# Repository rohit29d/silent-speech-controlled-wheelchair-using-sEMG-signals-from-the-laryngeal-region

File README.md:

# Hands-Free sEMG-Based Silent Speech Controlled Wheelchair System

[-blue?style=flat-square)](firmware/)

[-blue?style=flat-square)](ml_pipeline/)

> **Academic Notice**: This repository documents undergraduate capstone thesis research conducted at Amrita School of Engineering (March 2026). A formal manuscript publication currently in progress. All materials are shared for admissions review and non-commercial academic evaluation. For collaborative research access or hardware replication inquiries, please contact the author.

A complete end-to-end biomedical cyber-physical assistive system translating non-auditory surface electromyography (sEMG) bio-potentials from laryngeal musculature into real-time directional commands for an electric wheelchair. 

The architecture encompasses a custom multi-stage discrete Analog Front-End (AFE) PCB, an 8 kHz signal acquisition and digital feature extraction pipeline, a Bayesian-optimized Random Forest classifier, and a real-time embedded motor controller with ultrasonic safety interrupts implemented on an ARM Cortex-M7 microcontroller.

---

## System Overview & Clinical Motivation

Conventional assistive interfaces such as mechanical joysticks, sip-and-puff switches, or acoustic voice recognition present severe operational constraints for individuals with profound motor and speech impairments (e.g., Amyotrophic Lateral Sclerosis, locked-in syndrome, quadriplegia). While prior systems investigate ocular tracking, head gestures, or limb electromyography, individuals with advanced quadriplegia combined with vocal cord impairment retain intact cranial nerve pathways governing laryngeal and submental musculature.

During silent articulation (mouthing navigation words without acoustic vocalization), intrinsic and extrinsic laryngeal muscles produce repeatable neuromuscular bio-potentials. Capturing these microvolt signals via a dedicated, low-noise analog front-end provides an acoustic-noise-immune human-machine interface for powered wheelchair navigation.

> **Feasibility & Engineering Scope**: This system serves as a proof-of-concept feasibility platform demonstrating that laryngeal sEMG signals can reliably actuate an electric wheelchair in real time. While clinical adoption warrants non-invasive conformal electrode housings, this work proves that closed-loop silent articulation classification is achievable on embedded microcontroller hardware.

```
+-------------------------------------------------------------------------------------------------------------------------+
|                                                END-TO-END SYSTEM PIPELINE                                               |
+-------------------------------------------------------------------------------------------------------------------------+
```

---

## 1. Hardware & Analog Front-End (AFE)

Laryngeal sEMG signals exhibit low amplitudes ($\approx 10\ \mu\text{V} - 500\ \mu\text{V}$) and are highly vulnerable to motion artifacts, electrode polarization drift, and 50 Hz electromagnetic power-line interference. A dedicated 3-stage analog front-end was designed, simulated in LTspice, and fabricated as a compact 2-layer PCB.

### Circuit Topology & Component Selection

1. **Electrode Configuration**:
   - Differential 3-electrode montage using clinical-grade Ag/AgCl wet gel patches: two electrodes placed over the submental and ventromedial laryngeal muscles (thyrohyoid and sternohyoid) and a reference electrode placed on the cheekbone to establish a stable body ground.
2. **Discrete Instrumentation Amplifier (LM324)**:
   - Three-op-amp instrumentation topology chosen for high input impedance ($> 10^{10}\ \Omega$) to prevent signal attenuation from skin-electrode contact impedance.
   - Comparative operational amplifier testing across LM324, LM348, LM386, and $\mu\text{A}741$ established **LM324** as the optimal candidate due to its minimal output offset voltage of **0.199 mV** at high gain ($A_v = 1001$).
   - Implemented with 1% metal film resistors ($R_2, R_4 = 100\ \text{k}\Omega$, $R_1, R_3 = 10\ \text{k}\Omega$, $R_{\text{gain}} = 1\ \text{k}\Omega$) providing a Common-Mode Rejection Ratio (CMRR) designed for **100 dB**.
3. **Active Bandpass Filter Stage**:
   - Cascaded 20 Hz high-pass and 300 Hz low-pass sections in a Multiple Feedback / KRC topology forming a **6th-order Bessel filter**.
   - Bessel characteristics were selected over Butterworth and Chebyshev to achieve a maximally linear phase response and constant group delay, preserving the time-domain morphology of sEMG muscle bursts.
4. **50 Hz Twin-T Active Notch Filter**:
   - High-$Q$ band-reject KRC active filter providing sharp attenuation strictly centered at 50 Hz to reject power-line interference.
5. **Physical PCB Implementation**:
   - Compact 2-layer board measuring **6 cm × 2.5 cm**, routed with 0.2 mm signal traces and 0.3 mm power traces.
   - 0805 SMD components with inter-stage isolation jumpers and diagnostic test points for modular bench validation.
   - Conditioned bio-potentials produce a peak-to-peak output swing of **$\pm 0.8\ \text{V}$**, ready for digitizer ADC interfacing.

*Complete KiCad schematics, layouts, interactive BOM, and LTspice simulation models are organized in the [`hardware/`](hardware/) directory.*

---

## 2. Signal Preprocessing & Signal-to-Noise Enhancement

Digitized at $f_s = 8\ \text{kHz}$ via a Measurement Computing USB-1808 DAQ (18-bit resolution, low-latency streaming), the raw non-stationary signals undergo a two-stage software conditioning pipeline:

1. **Adaptive Discrete Wavelet Transform (DWT)**:
   - 6th-level multiresolution decomposition utilizing nearly-symmetric **Daubechies-6 (`db6`)** wavelets to minimize phase distortion.
   - **BayesShrink** data-driven adaptive thresholding applied to detail coefficients to eliminate in-band Gaussian noise.
   - Inverse DWT reconstruction preserves sharp physiological contraction onsets while eliminating high-frequency noise.
2. **Secondary Digital Bandpass**:
   - 4th-order Butterworth digital bandpass filter ($20\ \text{Hz} - 350\ \text{Hz}$) to isolate the low-frequency envelope where speech muscle activation is concentrated.

### Quantitative Noise Reduction Performance

| Metric | Raw Acquired Signal | Post-Denoised Signal | Improvement |
| :--- | :--- | :--- | :--- |
| **Signal-to-Noise Ratio (SNR)** | **2.43 dB** | **10.63 dB** | **+8.20 dB gain** |
| **Signal Morphology** | Heavy baseline drift & Gaussian noise | Clean contraction bursts with smooth envelope | Validated across 60 subjects |

---

## 3. Dataset & Data Augmentation

To ensure generalization across users while compensating for limited patient access, a comprehensive empirical dataset was acquired:

* **Cohort**: **60 human participants** (36 males, 4 females, aged 19–22).
* **Command Vocabulary**: 6 navigational directives: `FRONT`, `BACK`, `LEFT`, `RIGHT`, `START`, and `STOP`.
* **Articulatory Modalities**: Both audible vocalization and completely silent mouthing (words mouthed without acoustic sound).
* **Data Augmentation**: Applied exclusively to the 80% training partition using three random transformations:
  - Time Shifting (up to $\pm 10\%$ duration shift).
  - Time Scaling (duration compression/expansion between $80\% - 125\%$).
  - Frequency Warping via Short-Time Fourier Transform (STFT) to simulate inter-subject muscle conduction velocity differences.
* **Dataset Scale**: **14,598 balanced feature samples** across all 6 classes (80% train: 11,678 samples; 20% held-out test: 2,920 samples).
* **Benchmark Cross-Validation**: Validated against benchmark records from the **NIH Laryngeal sEMG Repository** (NIDCD Grant R15DC015335).

---

## 4. Feature Extraction & Selection

Feature extraction was performed using a **1000 ms sliding window**. A total of **32 distinct physiological descriptors** were computed across three analytical domains:

* **Time-Domain Descriptors**: Mean Absolute Value (MAV), Variance (VAR), Root Mean Square (RMS), Slope Sign Changes (SSC), Zero Crossings (ZC), Waveform Length (WL), Skewness, Kurtosis, Peak-to-Peak Amplitude, Zero-Crossing Rate, Mean, Shape Factor, Impulse Factor, Logarithmic Variance.
* **Frequency-Domain Descriptors**: Peak Frequency, Power Spectral Density (PSD), Band Power, Spectral Roll-Off, Spectral Spread, Mean Frequency (MNF), Median Frequency (MDF), Power Ratio, Spectral Centroid Ratio, Spectral Entropy Concentration, Spectral Entropy, Total Power.
* **Energy & Parametric Descriptors**: Teager-Kaiser Energy Operator statistics (TKEO: MAV, RMS, STD), Sub-band Power Ratios (Low, Mid, High), 4th-order Autoregressive (AR) coefficients.

### Feature Importance via ANOVA
One-way Analysis of Variance (**ANOVA $F$-statistic ranking**) was implemented to evaluate feature separability. While the full 32-feature vector was leveraged for high-accuracy host inference, the ANOVA ranking provides the exact mathematical basis for pruning the feature set down for resource-constrained microcontroller deployment.

---

## 5. Classifier Optimization & Quantitative Results

### Hyperparameter Tuning via Bayesian Optimization
Rather than relying on manual grid search, a **Bayesian Optimization algorithm (`BayesSearchCV`)** was executed over 50 iterations with 3-fold stratified cross-validation to locate the optimal hyperparameter manifold:

| Parameter | Setting / Optimal Value |
| :--- | :--- |
| **Estimators (`n_estimators`)** | 100 |
| **Maximum Depth (`max_depth`)** | 15 |
| **Max Features (`max_features`)** | `sqrt` |
| **Min Samples Split (`min_samples_split`)** | 20 |
| **Min Samples Leaf (`min_samples_leaf`)** | 7 |
| **Bootstrap** | False |

### Held-Out Test Set Performance (Unseen 2,920 Samples)

The optimized Random Forest classifier was evaluated on the completely unseen 20% held-out test partition:

| Navigation Command | Precision | Recall | F1-Score | Support |
| :--- | :---: | :---: | :---: | :---: |
| **FRONT** | 0.86 | 0.85 | 0.86 | 486 |
| **BACK** | 0.82 | 0.87 | 0.84 | 489 |
| **LEFT** | 0.91 | 0.88 | 0.90 | 487 |
| **RIGHT** | 0.89 | 0.86 | 0.88 | 486 |
| **START** | 0.91 | 0.90 | 0.91 | 486 |
| **STOP** | 0.89 | 0.91 | 0.90 | 486 |
| **Overall Model Metrics** | **Accuracy: 88.01%** | **Macro F1: 88.03%** | **3-Fold CV: 84.45% (±1.02%)** | **Total: 2,920** |

* The model demonstrates balanced diagonal separability across all classes, maintaining high precision ($> 0.89$) on critical navigational commands (`START`, `STOP`, `LEFT`).
* In offline testing across arbitrary pre-recorded streams, the classifier exhibited an average frame consistency of **72%**.

---

## 6. Real-Time Embedded Controller & Safety Architecture

The physical wheelchair actuation is governed by an **STM32H753ZI** microcontroller (ARM Cortex-M7 running at 480 MHz, double-precision FPU, 2 MB Flash, 1 MB RAM with ITCM/DTCM tightly coupled memory for zero-wait-state execution).

```
Serial Telemetry ---> Heartbeat Reset ---> Ultrasonic Echo Timing ---> Interrupt Override ---> BTS7960 Motor Drive
```

### Real-Time Inference & Gating Protocol

1. **"Wait-and-Classify" Streaming Loop**:
   - Host execution pauses polling until a **250 ms observation buffer** fills, applying a **50 ms timing interval** and **5 ms thread suspension** to eliminate buffer underruns and prevent CPU overutilization.
2. **Adaptive Noise Gate**:
   - An adaptive Root Mean Square gate continuously monitors the baseline noise floor; frames falling below twice the noise floor (or $< 0.005\ \text{V}$) are suppressed as quiescent muscle silence.
3. **21-Frame Temporal Majority Voting**:
   - Predictions meeting a minimum confidence probability ($P > 0.55$) enter a **21-frame FIFO circular buffer** (**1050 ms temporal smoothing window**).
   - Actuation is triggered if and only if a consensus of at least **15 matching frames** is achieved, mathematically rejecting spurious transitory twitches.
4. **Hardware Watchdog Heartbeat Failsafe**:
   - A hardware timer monitors UART communication latency: if no valid command frame arrives within **500 ms**, the microcontroller immediately cuts drive output and halts the wheelchair.
5. **DWT Hardware Microsecond Ultrasonic Safety Reflex**:
   - Forward and rear HC-SR04 ultrasonic rangefinders are polled using the ARM Data Watchpoint and Trace cycle counter (`DWT->CYCCNT`) for sub-microsecond timing accuracy.
   - If an obstacle is detected within **50 cm** during active motion, the interrupt safety logic instantly overrides host commands and brings the wheelchair to a stop. Resumption requires obstacle clearance plus a 0.5-second safety pause.
6. **High-Power Motor Actuation**:
   - Dual **BTS7960** high-current H-bridges (rated up to **43 A peak**, with thermal, over-current, and short-circuit protection) driven via differential PWM.
   - Actuating automotive-grade high-torque power window motors (ACI 83094) powered by a 12V lead-acid battery pack.

---

## 7. Experimental Demonstration & Video Archive

Complete system integration was validated through live user trials:
1. **Benchtop Acquisition & Denoising**: Verification of microvolt laryngeal bursts against environmental noise.
2. **Real-Time Classification Latency**: Predictable end-to-end command dispatch within 150 ms of articulation completion.
3. **Full-Scale Wheelchair Navigation**: Successful closed-loop indoor/outdoor test runs executing directional commands, pivot turns, and automated obstacle safety stops.

> ### 🎥 Full-Resolution Video Archive
> Due to repository size constraints, all 19 raw multi-angle demonstration recordings (~650 MB) are cataloged in our Google Drive repository:
> 
> **[Direct Link to Project Video Archive (Google Drive)](https://drive.google.com/drive/folders/1K86lcQrLWB6OToWdOsQsLnM8P3vR9gZU?usp=drive_link)**  
> *(Contains directories: `Prototype Results/`, `Real Time Prediction of sEMG signals/`, `Wheelchair operations with pre recorded commands/`, and `Wheelchair operations with real time commands/`)*

---

## 8. Repository Structure

```text
Hands-Free-sEMG-based-speech-controlled-wheelchair/
├── README.md                                  # Complete academic system documentation
├── LICENSE                                    # Showcase & Evaluation License (All Rights Reserved)
├── .gitignore                                 # Build rules for STM32, KiCad, Python, & media
│
├── hardware/                                  # ANALOG FRONT-END HARDWARE MODULE
│   ├── afe/                                   # KiCad EDA Project (Schematics & Layout)
│   │   ├── sEMG_AFE_V2.1.kicad_pro/          # Board files, symbols, footprint tables
│   │   │   ├── Filtering_stage.kicad_sch      # Active Bessel & Notch filter schematics
│   │   │   ├── instrumentation_amplifier.kicad_sch # 3-Op-Amp differential stage
│   │   │   ├── sEMG_AFE_V2.1.kicad_pro.kicad_pcb   # 2-Layer PCB layout
│   │   │   ├── Outputs/                       # Fabrication gerbers, drill files, iBOM
│   │   │   └── scripts/                       # Export automation scripts
│   │   ├── sEMG_pcb_schematic.pdf             # Standalone schematic document
│   │   └── README.md                          # Circuit stage design notes
│   └── simulations/                           # LTspice Simulation Models (.asc)
│       ├── bessel_final_4th_order_bpf.asc     # 4th-order active Bessel bandpass simulation
│       ├── intrs_amp.asc                      # Discrete instrumentation amplifier simulation
│       ├── Notch.asc                          # 50 Hz twin-T notch filter simulation
│       ├── Butterworth_filter.asc             # Butterworth comparison simulation
│       └── bessel_bpf_4_freq_resp.pdf         # AC sweep magnitude & phase response curves
│
├── firmware/                                  # EMBEDDED CONTROLLER FIRMWARE MODULE
│   └── stm32h7_controller/                    # STM32CubeIDE Project (ARM Cortex-M7)
│       └── model_testing/
│           ├── Core/
│           │   ├── Src/main.c                 # Control loop, UART parser, heartbeat watchdog
│           │   └── Inc/main.h                 # Pin allocations & hardware configuration
│           ├── Drivers/                       # STM32H7 HAL & CMSIS drivers
│           └── model_testing.ioc              # STM32CubeMX device initialization file
│
├── ml_pipeline/                               # MACHINE LEARNING & SIGNAL PROCESSING
│   ├── requirements.txt                       # Python dependencies
│   ├── run_pipeline.py                        # Automated feature extraction & training runner
│   ├── configs/settings.py                    # Acquisition frequency & windowing parameters
│   ├── src/
│   │   ├── preprocessing/                     # Butterworth filtering & wavelet denoising
│   │   ├── feature_extraction/                # 32 Time/Frequency/TKEO/AR extractors
│   │   ├── models/                            # Classifier training & cross-validation routines
│   │   └── inference/                         # Real-time serial streaming & prediction loop
│   └── outputs/                               # Evaluation plots (confusion matrices, models)
│
└── media/                                     # HIGH-RESOLUTION HARDWARE ASSETS
    ├── AFE_breadboard.jpeg                    # Breadboard experimental setup
    ├── IA_Notch.png                           # Instrumentation Amplifier & Notch schematic
    ├── bessle_BPF_order8.png                  # Bessel bandpass filter response
    ├── confusionsmatrix_RF.png                # Random Forest confusion matrix
    ├── samplesignal_timedomain.png            # Time-domain sEMG waveform
    └── samplesignal_spectraldomain.png        # Spectral-domain distribution
```

---

## Technical Author & Academic Affiliation

**Rohit Kumar Dubbaka**  
Department of Electronics and Communication Engineering (ECE)  
Amrita School of Engineering, Amrita Vishwa Vidyapeetham, Coimbatore  
*Collaborators*: Isukapalli Aditya, Harshath S  
*Faculty Advisor*: Ms. L. Vidhya  
*Email*: rohitdubbaka29@gmail.com | [LinkedIn](https://www.linkedin.com/in/rohit-kumar-dubbaka/) | [GitHub](https://github.com/rohit29d)  
*Academic Status*: B.Tech Capstone Thesis (March 2026).

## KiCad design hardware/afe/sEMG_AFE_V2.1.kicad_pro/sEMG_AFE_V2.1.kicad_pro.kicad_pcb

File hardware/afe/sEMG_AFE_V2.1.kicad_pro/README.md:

# sEMG_AFE_V2.1.kicad_pro

> Generated with export_fab_outputs.py v2.0.0

## 🚀 How to Use the Automation Script

### 🔧 Command Line (Terminal)

Run the following command **from the project directory** (where `.kicad_pro` is located):

```bash
make
```

To generate a zip of Gerbers for fabrication:
```bash
make release
```

Or run the script directly:
```bash
python3 scripts/export_fab_outputs.py
```

---

### 3D Views
#### Top View

#### Bottom View

#### Perspective View

---

### Schematic
[sEMG_AFE_V2.1.kicad_pro_schematic.pdf](output/sEMG_AFE_V2.1.kicad_pro_schematic.pdf)

### BOM
[sEMG_AFE_V2.1.kicad_pro_BOM.xlsx](output/sEMG_AFE_V2.1.kicad_pro_BOM.xlsx)

### Top Assembly
[sEMG_AFE_V2.1.kicad_pro_Top_Assembly.pdf](output/sEMG_AFE_V2.1.kicad_pro_Top_Assembly.pdf)

### Bottom Assembly
[sEMG_AFE_V2.1.kicad_pro_Bottom_Assembly.pdf](output/sEMG_AFE_V2.1.kicad_pro_Bottom_Assembly.pdf)

### Gerbers & Drill Files
[Gerbers/](output/Gerbers)

### Pick & Place
[sEMG_AFE_V2.1.kicad_pro-all-pos.csv](output/Gerbers/sEMG_AFE_V2.1.kicad_pro-all-pos.csv)

### Interactive BOM
Download and open [ibom.html](output/ibom/ibom.html) in browser

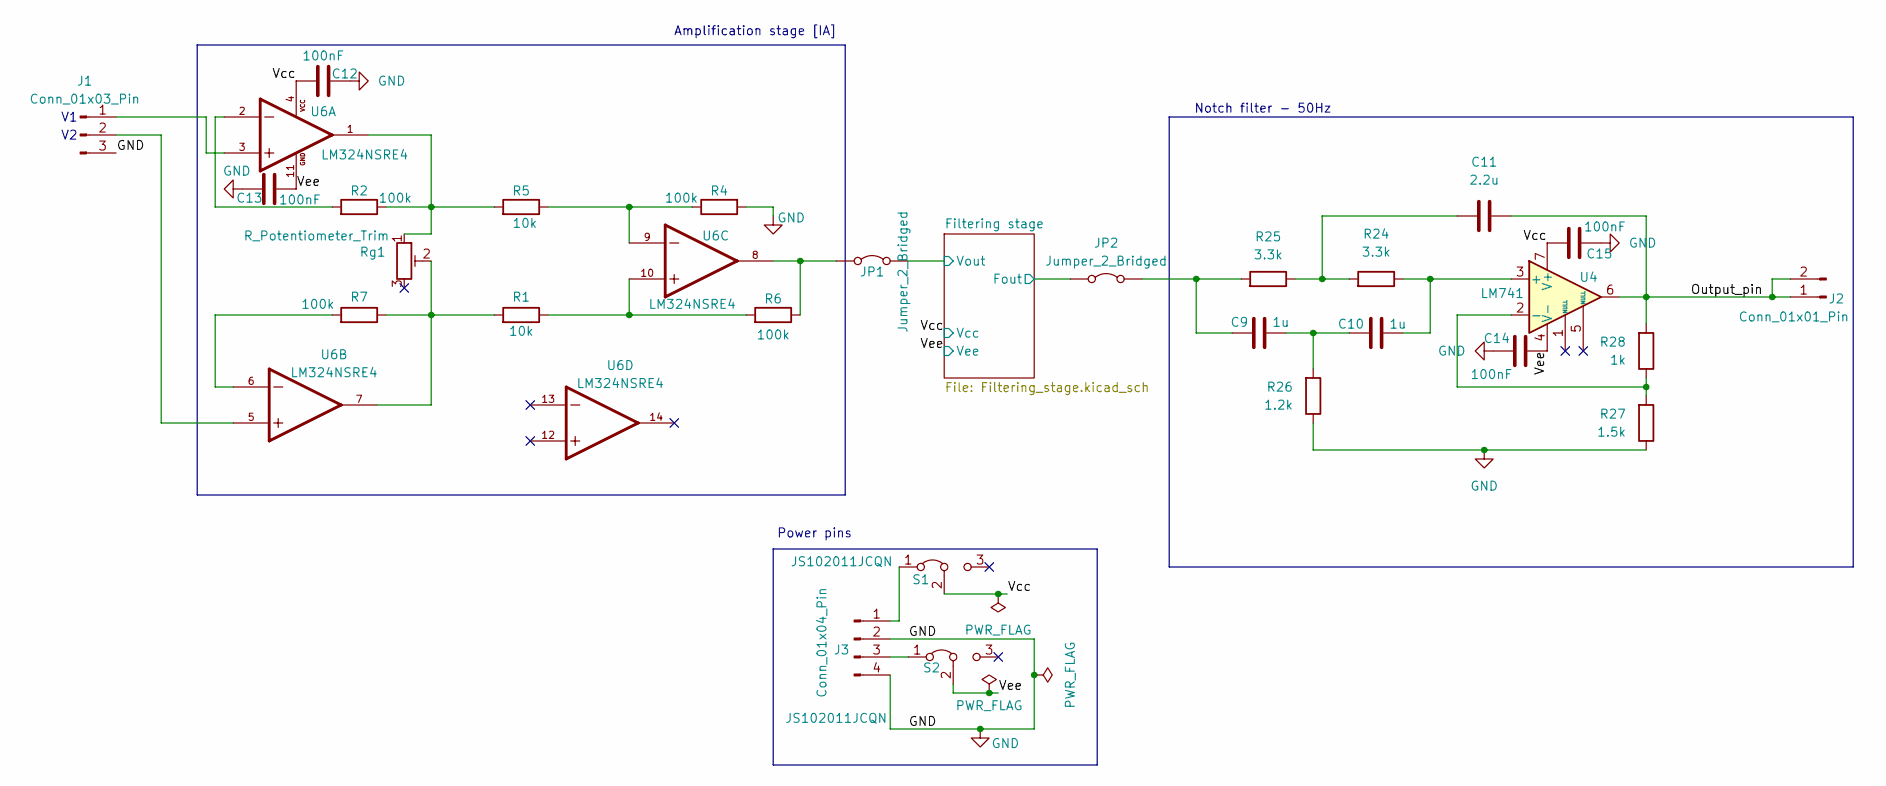
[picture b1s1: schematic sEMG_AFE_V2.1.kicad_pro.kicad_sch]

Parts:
C9, C10: 1u; C_0805_2012Metric
C11: 2.2u; C_0805_2012Metric
C12, C13, C14, C15: 100nF; C_0805_2012Metric
J1: Conn_01x03_Pin; JST_EH_B3B-EH-A_1x03_P2.50mm_Vertical
J2: Conn_01x01_Pin; JST_EH_B2B-EH-A_1x02_P2.50mm_Vertical
J3: Conn_01x04_Pin; TerminalBlock_Xinya_XY308-2.54-4P_1x04_P2.54mm_Horizontal
JP1, JP2: Jumper_2_Bridged; PinHeader_1x02_P2.54mm_Vertical
R1, R5: 10k; R_0805_2012Metric
R2, R4, R6, R7: 100k; R_0805_2012Metric
R24, R25: 3.3k; R_0805_2012Metric
R26: 1.2k; R_0805_2012Metric
R27: 1.5k; R_0805_2012Metric
R28: 1k; R_0805_2012Metric
Rg1: R_Potentiometer_Trim; Potentiometer_Bourns_3314G_Vertical
S1, S2: JS102011JCQN; PinHeader_1x03_P2.54mm_Vertical; PARTREV 29 JUN 2016
U4: LM741; JEITA_SOIC-8_3.9x4.9mm_P1.27mm
U6: LM324NSRE4; SOIC127P780X200-14N; PARTREV W

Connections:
/Filtering stage/Fout: JP2.1 (A); also elsewhere on the board
/Filtering stage/Vout: JP1.2 (B); also elsewhere on the board
/Output_pin: C11.2, J2.1, J2.2, R28.2, U4.6
/Vcc: C12.1, C15.1, S1.2 (C), U4.7 (V+), U6.4; also elsewhere on the board
/Vee: C13.2, C14.2, S2.2 (C), U4.4 (V-), U6.11; also elsewhere on the board
GND: C12.2, C13.1, C14.1, C15.2, J1.3, J3.2, J3.4, R4.2, R26.1, R27.1; also elsewhere on the board
unnamed: C9.2, C10.1, R26.2
unnamed: C11.1, R24.2, R25.1
unnamed: J1.1, U6.3
unnamed: J1.2, U6.5
unnamed: J3.1, S1.1 (A)
unnamed: J3.3, S2.1 (A)
unnamed: JP1.1 (A), R6.1, U6.8
unnamed: C9.1, JP2.2 (B), R25.2
unnamed: R1.1, R6.2, U6.10
unnamed: R1.2, R7.1, Rg1.2, U6.7
unnamed: R2.1, R5.2, Rg1.1, U6.1
unnamed: R2.2, U6.2
unnamed: R4.1, R5.1, U6.9
unnamed: R7.2, U6.6
unnamed: C10.2, R24.1, U4.3 (+)
unnamed: R27.2, R28.1, U4.2 (-)

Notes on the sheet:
Amplification stage [IA]
Power pins
Notch filter - 50Hz

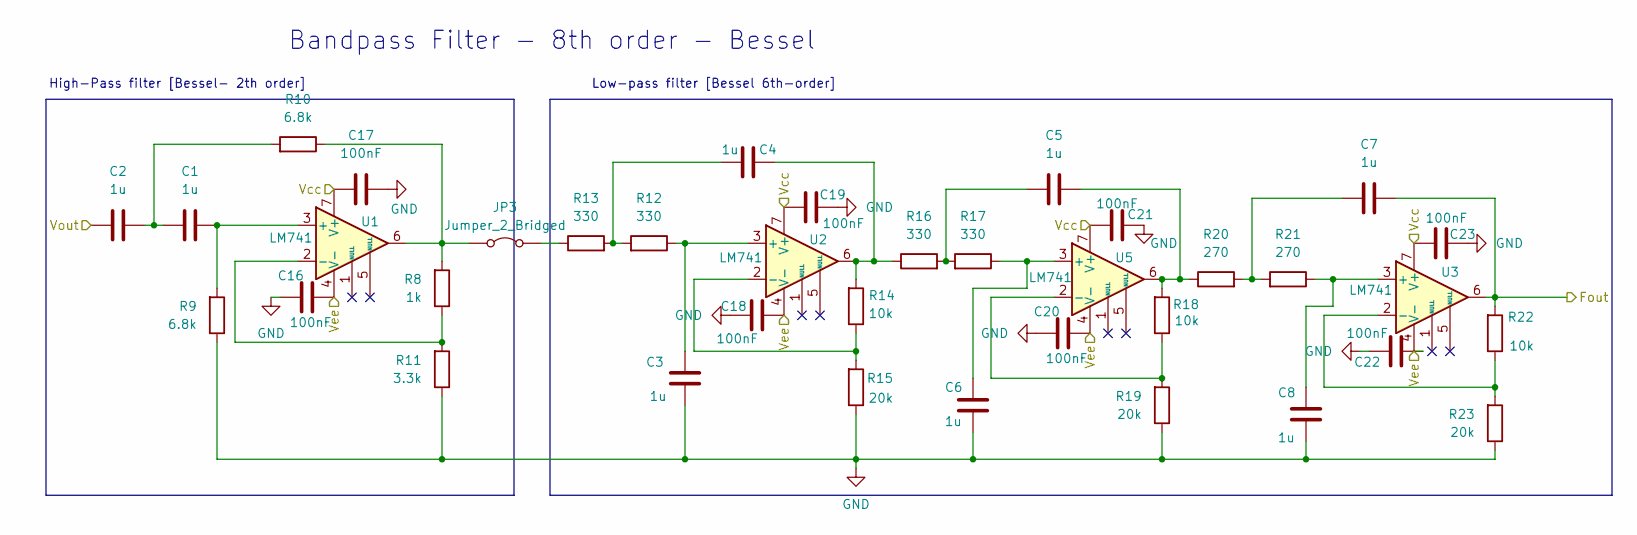
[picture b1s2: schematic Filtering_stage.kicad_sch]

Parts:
C1, C2, C3, C4, C5, C6, C7, C8: 1u; C_0805_2012Metric
C16, C17, C18, C19, C20, C21, C22, C23: 100nF; C_0805_2012Metric
JP3: Jumper_2_Bridged; PinHeader_1x02_P2.54mm_Vertical
R8: 1k; R_0805_2012Metric
R9, R10: 6.8k; R_0805_2012Metric
R11: 3.3k; R_0805_2012Metric
R12, R13, R16, R17: 330; R_0805_2012Metric
R14, R18, R22: 10k; R_0805_2012Metric
R15, R19, R23: 20k; R_0805_2012Metric
R20, R21: 270; R_0805_2012Metric
U1, U2, U3, U5: LM741; JEITA_SOIC-8_3.9x4.9mm_P1.27mm

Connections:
/Filtering stage/Fout: C7.2, R22.2, U3.6; also elsewhere on the board
/Filtering stage/Vout: C2.1; also elsewhere on the board
/Vcc: C17.1, C19.1, C21.1, C23.1, U1.7 (V+), U2.7 (V+), U3.7 (V+), U5.7 (V+); also elsewhere on the board
/Vee: C16.2, C18.2, C20.2, C22.2, U1.4 (V-), U2.4 (V-), U3.4 (V-), U5.4 (V-); also elsewhere on the board
GND: C3.1, C6.1, C8.1, C16.1, C17.2, C18.1, C19.2, C20.1, C21.2, C22.1, C23.2, R9.1, R11.1, R15.1, R19.1, R23.1; also elsewhere on the board
unnamed: C1.1, C2.2, R10.2
unnamed: C4.1, R12.2, R13.2
unnamed: C4.2, R14.2, R16.1, U2.6
unnamed: C5.1, R16.2, R17.2
unnamed: C5.2, R18.2, R20.1, U5.6
unnamed: C7.1, R20.2, R21.2
unnamed: JP3.1 (A), R8.2, R10.1, U1.6
unnamed: JP3.2 (B), R13.1
unnamed: C1.2, R9.2, U1.3 (+)
unnamed: R8.1, R11.2, U1.2 (-)
unnamed: C3.2, R12.1, U2.3 (+)
unnamed: R14.1, R15.2, U2.2 (-)
unnamed: C8.2, R21.1, U3.3 (+)
unnamed: R22.1, R23.2, U3.2 (-)
unnamed: C6.2, R17.1, U5.3 (+)
unnamed: R18.1, R19.2, U5.2 (-)

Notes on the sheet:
Low-pass filter [Bessel 6th-order]
Bandpass Filter - 8th order - Bessel
High-Pass filter [Bessel- 2th order]

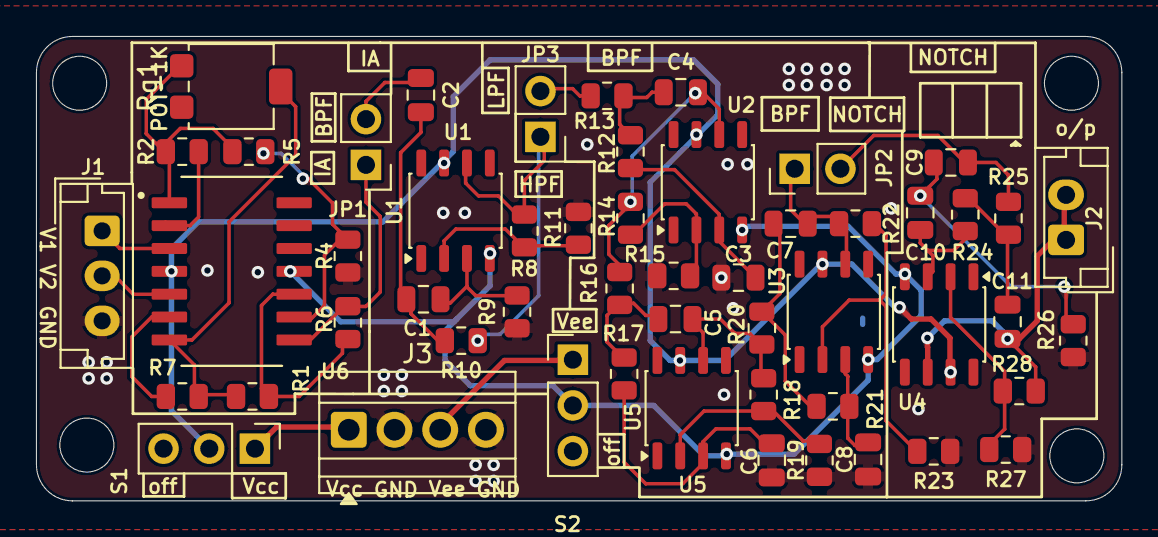
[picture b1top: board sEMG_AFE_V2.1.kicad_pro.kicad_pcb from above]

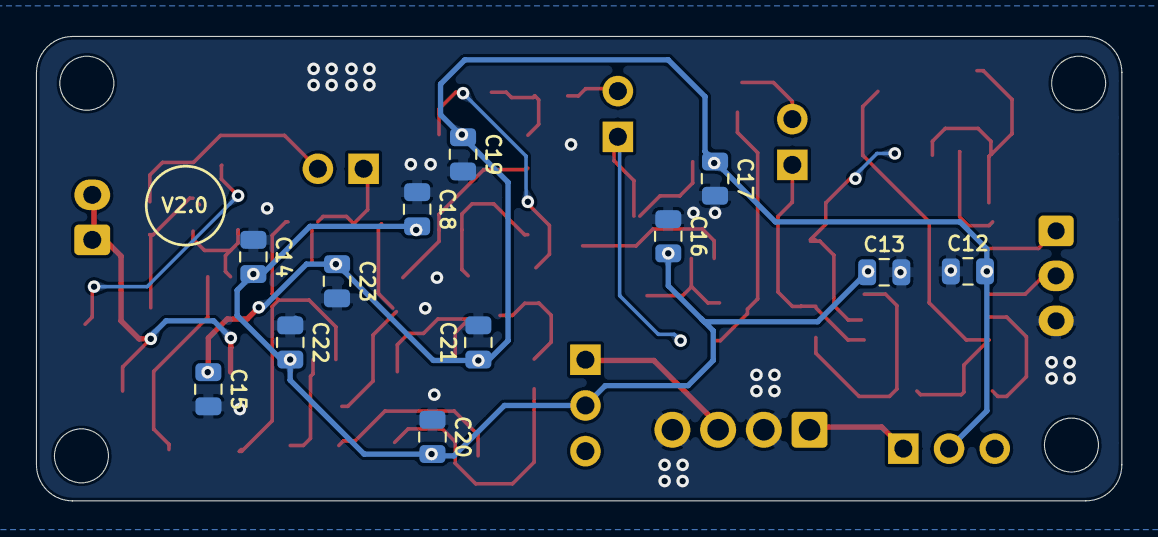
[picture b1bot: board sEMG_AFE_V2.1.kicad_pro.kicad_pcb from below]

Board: 2 copper layers, 60.3 x 25.8 mm, 65 parts (12 on the bottom side), 38 nets.

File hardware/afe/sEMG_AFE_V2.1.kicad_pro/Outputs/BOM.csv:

"Reference","Qty","Value","DNP","Exclude from BOM","Exclude from Board","Footprint","Datasheet"
"C1,C2,C3,C4,C5,C6,C7,C8,C9,C10","10","1u","","","","Capacitor_SMD:C_1206_3216Metric","~"
"C11","1","2.2u","","","","Capacitor_SMD:C_1206_3216Metric","~"
"H1","1","VCC","","Excluded from BOM","","MountingHole:MountingHole_2.2mm_M2_DIN965_Pad_TopBottom","~"
"H2","1","VEE","","Excluded from BOM","","MountingHole:MountingHole_2.2mm_M2_DIN965_Pad_TopBottom","~"
"H3","1","GND","","Excluded from BOM","","MountingHole:MountingHole_2.2mm_M2_DIN965_Pad_TopBottom","~"
"H4","1","I/P_1","","Excluded from BOM","","MountingHole:MountingHole_2.2mm_M2_DIN965_Pad_TopBottom","~"
"H5","1","I/P_2","","Excluded from BOM","","MountingHole:MountingHole_2.2mm_M2_DIN965_Pad_TopBottom","~"
"H6","1","GND2","","Excluded from BOM","","MountingHole:MountingHole_2.2mm_M2_DIN965_Pad_TopBottom","~"
"H7","1","Output","","Excluded from BOM","","MountingHole:MountingHole_2.2mm_M2_DIN965_Pad_TopBottom","~"
"J2","1","Conn_01x14_Pin","","","","Package_SO:SOIC-14_3.9x8.7mm_P1.27mm","~"
"JP1,JP2","2","Jumper_2_Bridged","","","","Connector_PinHeader_2.54mm:PinHeader_1x02_P2.54mm_Vertical","~"
"R1,R5,R14,R18,R22","5","10k","","","","Resistor_SMD:R_1206_3216Metric","~"
"R2,R4,R6,R7","4","100k","","","","Resistor_SMD:R_1206_3216Metric","~"
"R3,R8,R28","3","1k","","","","Resistor_SMD:R_1206_3216Metric","~"
"R9,R10","2","6.8k","","","","Resistor_SMD:R_1206_3216Metric","~"
"R11,R24,R25","3","3.3k","","","","Resistor_SMD:R_1206_3216Metric","~"
"R12,R13,R16,R17","4","330","","","","Resistor_SMD:R_1206_3216Metric","~"
"R15,R19,R23","3","20k","","","","Resistor_SMD:R_1206_3216Metric","~"
"R20,R21","2","270","","","","Resistor_SMD:R_1206_3216Metric","~"
"R26","1","1.2k","","","","Resistor_SMD:R_1206_3216Metric","~"
"R27","1","1.5k","","","","Resistor_SMD:R_1206_3216Metric","~"
"U1,U2,U3,U4,U5","5","LM741","","","","Package_SO:JEITA_SOIC-8_3.9x4.9mm_P1.27mm","http://www.ti.com/lit/ds/symlink/lm741.pdf"

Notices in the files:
README.md:
License: Academic Research & Evaluation
